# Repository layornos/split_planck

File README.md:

# Custom Keyboard - Split Ortholinear Keyboard (split planck)

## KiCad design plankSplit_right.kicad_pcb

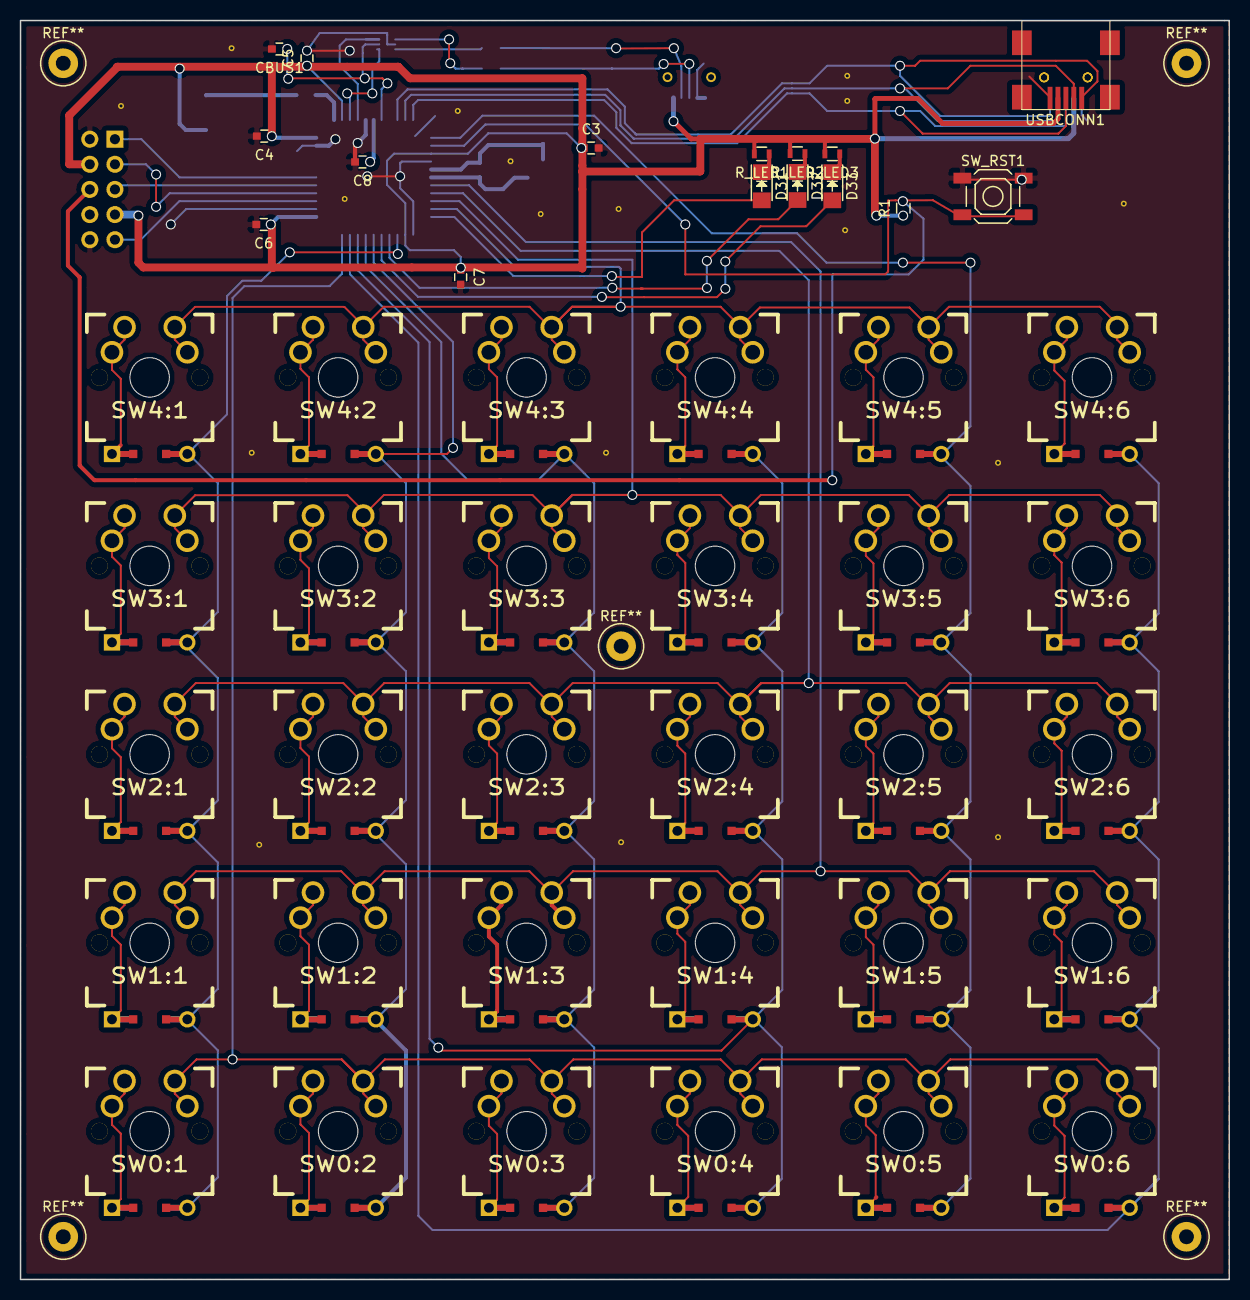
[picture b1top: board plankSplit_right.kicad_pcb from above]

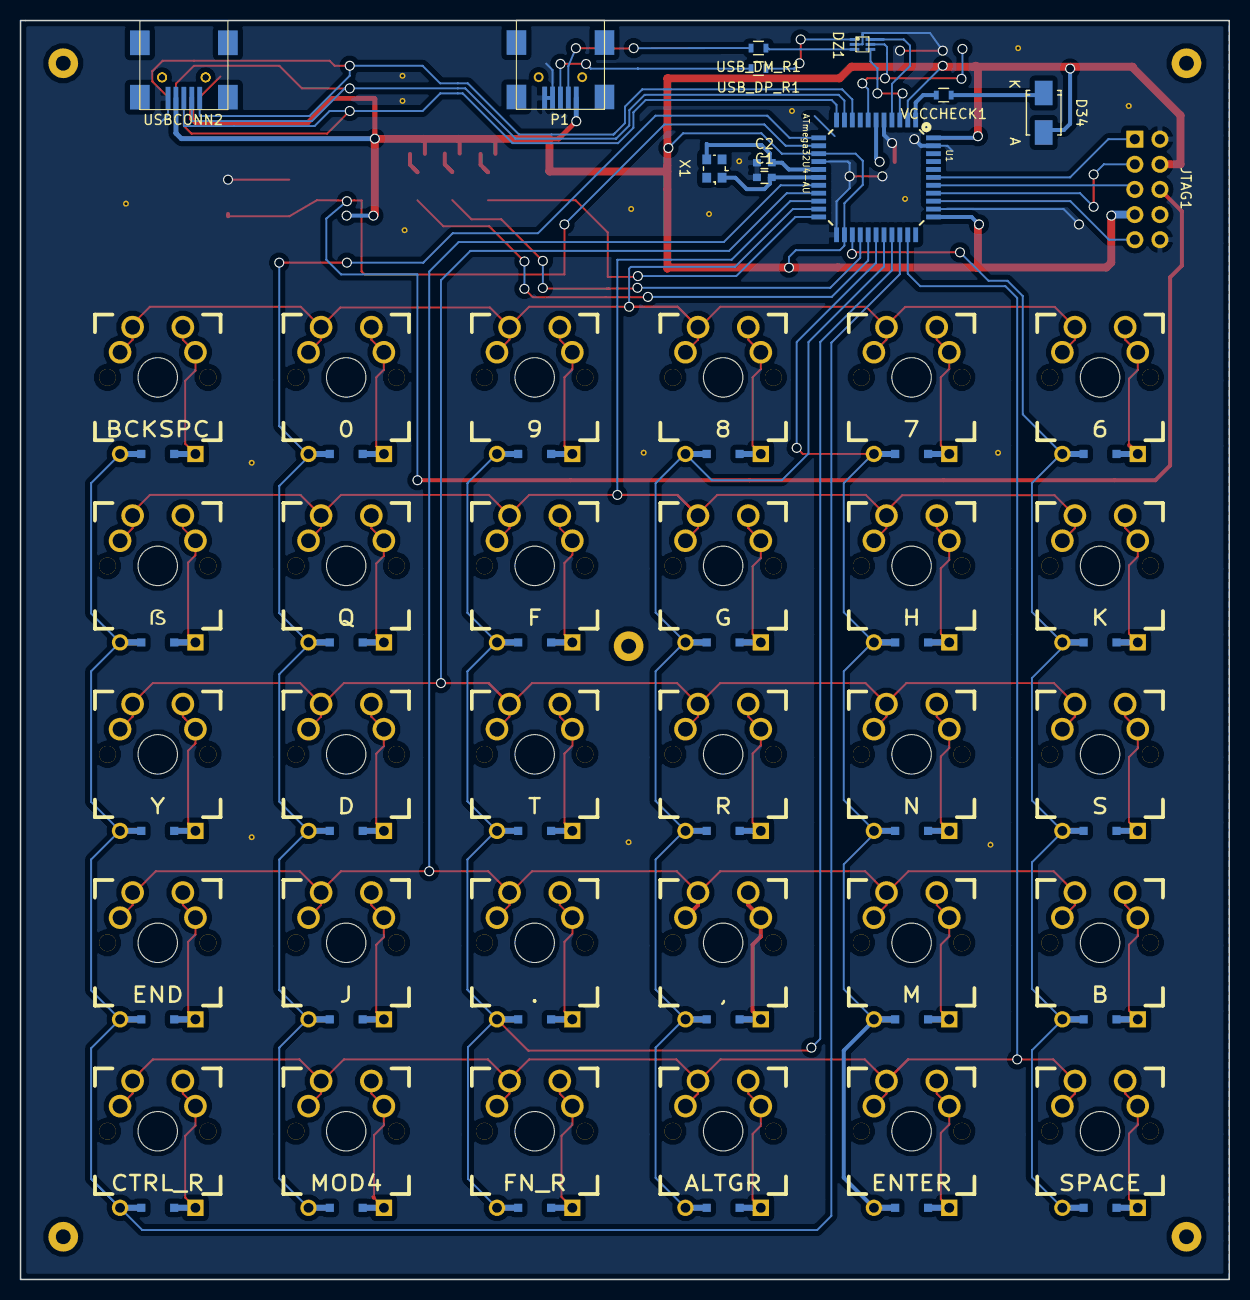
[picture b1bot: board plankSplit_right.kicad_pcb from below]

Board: 2 copper layers, 122.2 x 127.3 mm, 88 parts (12 on the bottom side), 69 nets.

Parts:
C1, C2: 22pF; C_0603
C3, C4, C5, C6, C7: 100nF; C_0603
C8: 1uF; C_0603
CBUS1: 100nF; C_0603
D1: D4:0; DIODE
D2: D3:0; DIODE
D3: D2:0; DIODE
D4: D1:0; DIODE
D5: D0:0; DIODE
D6: D4:1; DIODE
D7: D3:1; DIODE
D8: D2:1; DIODE
D9: D1:1; DIODE
D10: D0:1; DIODE
D11: D4:2; DIODE
D12: D3:2; DIODE
D13: D2:2; DIODE
D14: D1:2; DIODE
D15: D0:2; DIODE
D16: D4:3; DIODE
D17: D3:3; DIODE
D18: D2:3; DIODE
D19: D1:3; DIODE
D20: D0:3; DIODE
D21: D4:4; DIODE
D22: D3:4; DIODE
D23: D2:4; DIODE
D24: D1:4; DIODE
D25: D0:4; DIODE
D26: D4:5; DIODE
D27: D3:5; DIODE
D28: D2:5; DIODE
D29: D1:5; DIODE
D30: D0:5; DIODE
D31, D32, D33: LED; LED_1206
D34: D; SMA_Standard
DZ1: USBLC6-2P6; usblc6-2p6
JTAG1: JTAG; IDC_Header_Straight_10pins
P1: USB_A; usb-b-mini-female
R1: 10k; R_0603
R_LED1, R_LED2, R_LED3: R220; R_0603
SW0:1: SPACE; MX_FLIP_DIODE_New
SW0:2: ENTER; MX_FLIP_DIODE_New
SW0:3: ALTGR; MX_FLIP_DIODE_New
SW0:4: FN_R; MX_FLIP_DIODE_New
SW0:5: MOD4; MX_FLIP_DIODE_New
SW0:6: CTRL_R; MX_FLIP_DIODE_New
SW1:1: B; MX_FLIP_DIODE_New
SW1:2: M; MX_FLIP_DIODE_New
SW1:3: ,; MX_FLIP_DIODE_New
SW1:4: .; MX_FLIP_DIODE_New
SW1:5: J; MX_FLIP_DIODE_New
SW1:6: END; MX_FLIP_DIODE_New
SW2:1: S; MX_FLIP_DIODE_New
SW2:2: N; MX_FLIP_DIODE_New
SW2:3: R; MX_FLIP_DIODE_New
SW2:4: T; MX_FLIP_DIODE_New
SW2:5: D; MX_FLIP_DIODE_New
SW2:6: Y; MX_FLIP_DIODE_New
SW3:1: K; MX_FLIP_DIODE_New
SW3:2: H; MX_FLIP_DIODE_New
SW3:3: G; MX_FLIP_DIODE_New
SW3:4: F; MX_FLIP_DIODE_New
SW3:5: Q; MX_FLIP_DIODE_New
SW3:6: ẞ; MX_FLIP_DIODE_New
SW4:1: 6; MX_FLIP_DIODE_New
SW4:2: 7; MX_FLIP_DIODE_New
SW4:3: 8; MX_FLIP_DIODE_New
SW4:4: 9; MX_FLIP_DIODE_New
SW4:5: 0; MX_FLIP_DIODE_New
SW4:6: BCKSPC; MX_FLIP_DIODE_New
SW_RST1: SWRST; SW_SPST_SKQG
U1: ATmega32U4-AU; TQFP44
USBCONN1, USBCONN2: CONN_5; usb-b-mini-female
USB_DM_R1: R; R_0603
USB_DP_R1: R; R_0603
VCCCHECK1: R47k; R_0603
X1: CRYSTAL; Crystal_SMD_2520_4Pads

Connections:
/COL0: D1.1, D2.1, D3.1, D4.1, D5.1, U1.25
/COL1: D6.1, D7.1, D8.1, D9.1, D10.1, U1.28
/COL2: D11.1, D12.1, D13.1, D14.1, D15.1, U1.29
/COL3: D16.1, D17.1, D18.1, D19.1, D20.1, U1.30
/COL4: D21.1, D22.1, D23.1, D24.1, D25.1, U1.12
/COL5: D26.1, D27.1, D28.1, D29.1, D30.1, U1.31
/D+in: DZ1.6, U1.4
/D+out: DZ1.1, USB_DP_R1.1
/D-in: DZ1.4, U1.3
/D-out: DZ1.3, USB_DM_R1.1
/DATA1: U1.10, USBCONN1.2, USBCONN2.2
/DATA2: U1.11, USBCONN1.3, USBCONN2.3
/LED1: D31.2, U1.22
/LED2: D32.2, U1.26
/LED3: D33.2, U1.27
/P1: U1.1, VCCCHECK1.2
/P14_VCC: C3.1, C4.1, C5.1, C6.1, C7.1, D34.2, JTAG1.4, JTAG1.7, P1.1, R1.1, R_LED1.2, R_LED2.2, R_LED3.2, U1.2, U1.14, U1.24, U1.34, U1.44, USBCONN1.4, USBCONN2.4
/ROW0: SW0:1.1, SW0:2.1, SW0:3.1, SW0:4.1, SW0:5.1, SW0:6.1, U1.32
/ROW1: SW1:1.1, SW1:2.1, SW1:3.1, SW1:4.1, SW1:5.1, SW1:6.1, U1.18
/ROW2: SW2:1.1, SW2:2.1, SW2:3.1, SW2:4.1, SW2:5.1, SW2:6.1, U1.19
/ROW3: SW3:1.1, SW3:2.1, SW3:3.1, SW3:4.1, SW3:5.1, SW3:6.1, U1.20
/ROW4: SW4:1.1, SW4:2.1, SW4:3.1, SW4:4.1, SW4:5.1, SW4:6.1, U1.21
/RST: JTAG1.6, R1.2, SW_RST1.2, U1.13
/SCLK: U1.9, USBCONN1.1, USBCONN2.1
/TCK: JTAG1.1, U1.39
/TDI: JTAG1.9, U1.36
/TDO: JTAG1.3, U1.37
/TMS: JTAG1.5, U1.38
/UCAP: C8.1, U1.6
/UGND: C1.1, C2.1, C3.2, C4.2, C5.2, C6.2, C7.2, C8.2, CBUS1.2, DZ1.2, JTAG1.2, JTAG1.10, P1.4, P1.5, SW_RST1.1, U1.5, U1.15, U1.23, U1.35, U1.43, USBCONN1.5, USBCONN2.5
/VBus: CBUS1.1, DZ1.5, U1.7
/XTAL1: C1.2, U1.17, X1.1
/XTAL2: C2.2, U1.16, X1.2
unnamed: D1.2, SW4:1.2
unnamed: D2.2, SW3:1.2
unnamed: D3.2, SW2:1.2
unnamed: D4.2, SW1:1.2
unnamed: D5.2, SW0:1.2
unnamed: D6.2, SW4:2.2
unnamed: D7.2, SW3:2.2
unnamed: D8.2, SW2:2.2
unnamed: D9.2, SW1:2.2
unnamed: D10.2, SW0:2.2
unnamed: D11.2, SW4:3.2
unnamed: D12.2, SW3:3.2
unnamed: D13.2, SW2:3.2
unnamed: D14.2, SW1:3.2
unnamed: D15.2, SW0:3.2
unnamed: D16.2, SW4:4.2
unnamed: D17.2, SW3:4.2
unnamed: D18.2, SW2:4.2
unnamed: D19.2, SW1:4.2
unnamed: D20.2, SW0:4.2
unnamed: D21.2, SW4:5.2
unnamed: D22.2, SW3:5.2
unnamed: D23.2, SW2:5.2
unnamed: D24.2, SW1:5.2
unnamed: D25.2, SW0:5.2
unnamed: D26.2, SW4:6.2
unnamed: D27.2, SW3:6.2
unnamed: D28.2, SW2:6.2
unnamed: D29.2, SW1:6.2
unnamed: D30.2, SW0:6.2
unnamed: D31.1, R_LED1.1
unnamed: D32.1, R_LED2.1
unnamed: D33.1, R_LED3.1
unnamed: D34.1, VCCCHECK1.1
unnamed: P1.2, USB_DM_R1.2
unnamed: P1.3, USB_DP_R1.2

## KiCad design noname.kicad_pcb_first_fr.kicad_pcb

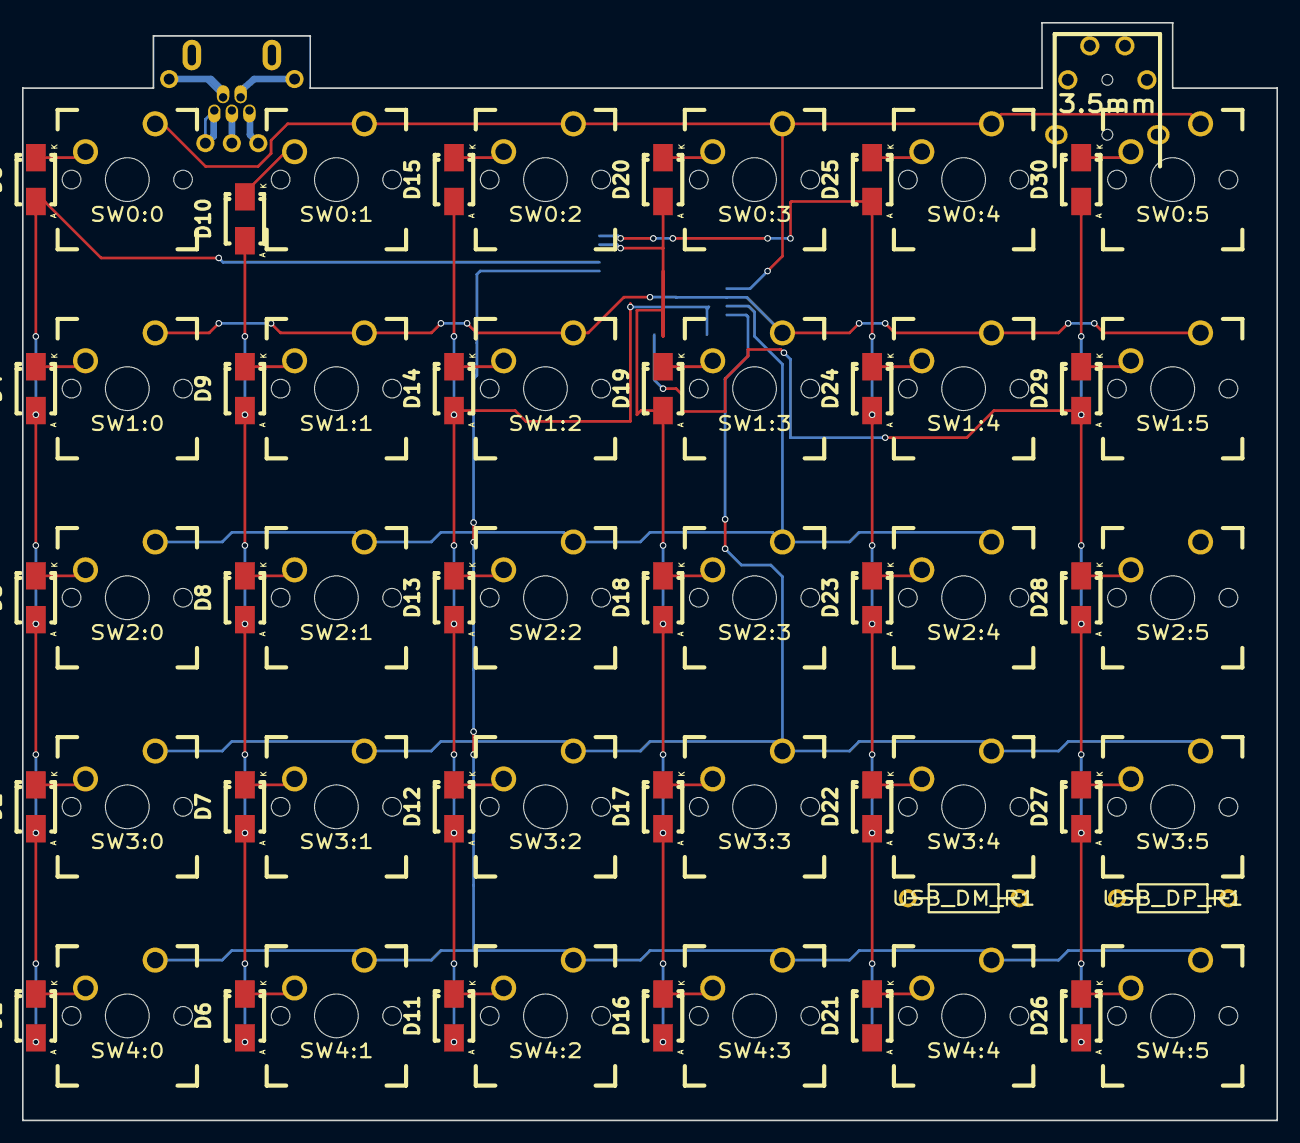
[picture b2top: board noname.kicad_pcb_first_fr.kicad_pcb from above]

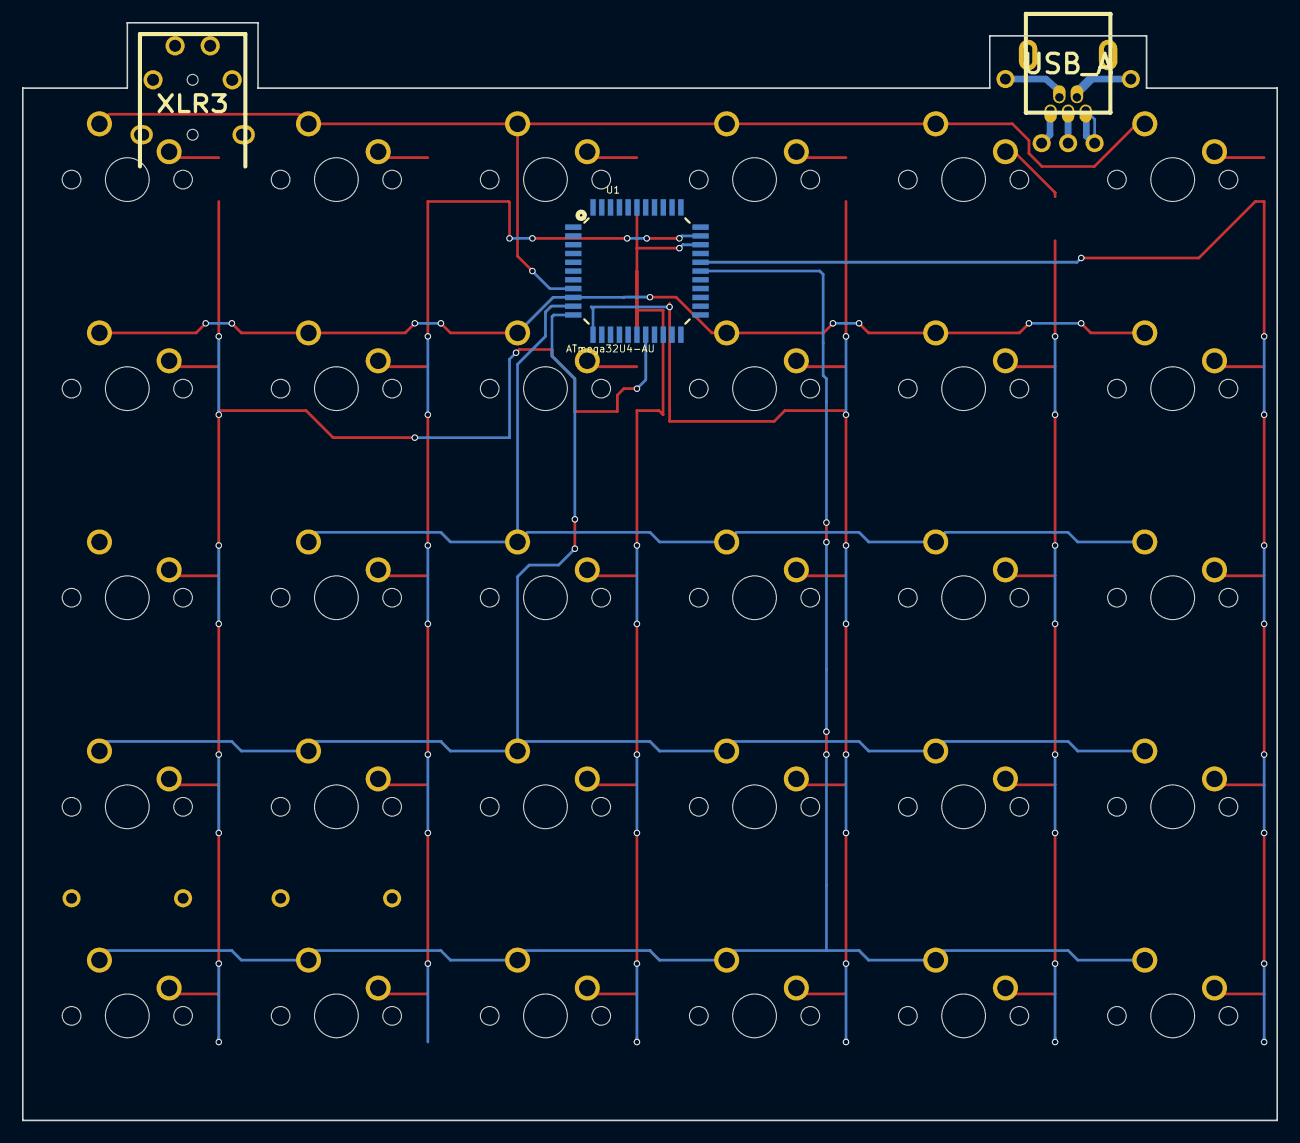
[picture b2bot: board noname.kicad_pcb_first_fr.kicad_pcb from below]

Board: 2 copper layers, 114.3 x 100.0 mm, 65 parts (3 on the bottom side), 46 nets.

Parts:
D1: D4:0; Diode-SMA_Standard_RevA_26July2010
D2: D3:0; Diode-SMA_Standard_RevA_26July2010
D3: D2:0; Diode-SMA_Standard_RevA_26July2010
D4: D1:0; Diode-SMA_Standard_RevA_26July2010
D5: D0:0; Diode-SMA_Standard_RevA_26July2010
D6: D4:1; Diode-SMA_Standard_RevA_26July2010
D7: D3:1; Diode-SMA_Standard_RevA_26July2010
D8: D2:1; Diode-SMA_Standard_RevA_26July2010
D9: D1:1; Diode-SMA_Standard_RevA_26July2010
D10: D0:1; Diode-SMA_Standard_RevA_26July2010
D11: D4:2; Diode-SMA_Standard_RevA_26July2010
D12: D3:2; Diode-SMA_Standard_RevA_26July2010
D13: D2:2; Diode-SMA_Standard_RevA_26July2010
D14: D1:2; Diode-SMA_Standard_RevA_26July2010
D15: D0:2; Diode-SMA_Standard_RevA_26July2010
D16: D4:3; Diode-SMA_Standard_RevA_26July2010
D17: D3:3; Diode-SMA_Standard_RevA_26July2010
D18: D2:3; Diode-SMA_Standard_RevA_26July2010
D19: D1:3; Diode-SMA_Standard_RevA_26July2010
D20: D0:3; Diode-SMA_Standard_RevA_26July2010
D21: D4:4; Diode-SMA_Standard_RevA_26July2010
D22: D3:4; Diode-SMA_Standard_RevA_26July2010
D23: D2:4; Diode-SMA_Standard_RevA_26July2010
D24: D1:4; Diode-SMA_Standard_RevA_26July2010
D25: D0:4; Diode-SMA_Standard_RevA_26July2010
D26: D4:5; Diode-SMA_Standard_RevA_26July2010
D27: D3:5; Diode-SMA_Standard_RevA_26July2010
D28: D2:5; Diode-SMA_Standard_RevA_26July2010
D29: D1:5; Diode-SMA_Standard_RevA_26July2010
D30: D0:5; Diode-SMA_Standard_RevA_26July2010
K1: XLR3; 4pin35mmAudio
P1: USB_A; USBMINImod
SW0:0: SPACE; CHERRY_PCB_100H
SW0:1: ENTER; CHERRY_PCB_100H
SW0:2: ALTGR; CHERRY_PCB_100H
SW0:3: FN_R; CHERRY_PCB_100H
SW0:4: MOD4; CHERRY_PCB_100H
SW0:5: CTRL_R; CHERRY_PCB_100H
SW1:0: B; CHERRY_PCB_100H
SW1:1: M; CHERRY_PCB_100H
SW1:2: ,; CHERRY_PCB_100H
SW1:3: .; CHERRY_PCB_100H
SW1:4: J; CHERRY_PCB_100H
SW1:5: END; CHERRY_PCB_100H
SW2:0: S; CHERRY_PCB_100H
SW2:1: N; CHERRY_PCB_100H
SW2:2: R; CHERRY_PCB_100H
SW2:3: T; CHERRY_PCB_100H
SW2:4: D; CHERRY_PCB_100H
SW2:5: Y; CHERRY_PCB_100H
SW3:0: K; CHERRY_PCB_100H
SW3:1: H; CHERRY_PCB_100H
SW3:2: G; CHERRY_PCB_100H
SW3:3: F; CHERRY_PCB_100H
SW3:4: Q; CHERRY_PCB_100H
SW3:5: ẞ; CHERRY_PCB_100H
SW4:0: 6; CHERRY_PCB_100H
SW4:1: 7; CHERRY_PCB_100H
SW4:2: 8; CHERRY_PCB_100H
SW4:3: 9; CHERRY_PCB_100H
SW4:4: 0; CHERRY_PCB_100H
SW4:5: BCKSPC; CHERRY_PCB_100H
U1: ATmega32U4-AU; TQFP44
USB_DM_R1: R; RESISTOR
USB_DP_R1: R; RESISTOR

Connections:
/COL0: D1.1, D2.1, D3.1, D4.1, D5.1, U1.29
/COL1: D6.1, D7.1, D8.1, D9.1, D10.1, U1.30
/COL2: D11.1, D12.1, D13.1, D14.1, D15.1, U1.12
/COL3: D16.1, D17.1, D18.1, D19.1, D20.1, U1.31
/COL4: D21.1, D22.1, D23.1, D24.1, D25.1, U1.32
/COL5: D26.1, D27.1, D28.1, D29.1, D30.1, U1.18
/DATA: K1.1, U1.19
/ROW0: SW0:0.1, SW0:1.1, SW0:2.1, SW0:3.1, SW0:4.1, SW0:5.1, U1.8
/ROW1: SW1:0.1, SW1:1.1, SW1:2.1, SW1:3.1, SW1:4.1, SW1:5.1, U1.9
/ROW2: SW2:0.1, SW2:1.1, SW2:2.1, SW2:3.1, SW2:4.1, SW2:5.1, U1.10
/ROW3: SW3:0.1, SW3:1.1, SW3:2.1, SW3:3.1, SW3:4.1, SW3:5.1, U1.11
/ROW4: SW4:0.1, SW4:1.1, SW4:2.1, SW4:3.1, SW4:4.1, SW4:5.1, U1.28
/USB_GND: P1.4, U1.5
/USB_VCC: P1.1, U1.2
GND: K1.3, U1.35
unnamed: D1.2, SW4:0.2
unnamed: D2.2, SW3:0.2
unnamed: D3.2, SW2:0.2
unnamed: D4.2, SW1:0.2
unnamed: D5.2, SW0:0.2
unnamed: D6.2, SW4:1.2
unnamed: D7.2, SW3:1.2
unnamed: D8.2, SW2:1.2
unnamed: D9.2, SW1:1.2
unnamed: D10.2, SW0:1.2
unnamed: D11.2, SW4:2.2
unnamed: D12.2, SW3:2.2
unnamed: D13.2, SW2:2.2
unnamed: D14.2, SW1:2.2
unnamed: D15.2, SW0:2.2
unnamed: D16.2, SW4:3.2
unnamed: D17.2, SW3:3.2
unnamed: D18.2, SW2:3.2
unnamed: D19.2, SW1:3.2
unnamed: D20.2, SW0:3.2
unnamed: D21.2, SW4:4.2
unnamed: D22.2, SW3:4.2
unnamed: D23.2, SW2:4.2
unnamed: D24.2, SW1:4.2
unnamed: D25.2, SW0:4.2
unnamed: D26.2, SW4:5.2
unnamed: D27.2, SW3:5.2
unnamed: D28.2, SW2:5.2
unnamed: D29.2, SW1:5.2
unnamed: D30.2, SW0:5.2
VCC: K1.2, U1.14

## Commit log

2016-08-06 init
2016-08-06 create rm
2016-08-06 added jtag and some capacitors
2016-08-06 margin updated
2016-08-07 Added more vias
2016-08-10 some footprints and track redraw
2016-09-07 Rev1.0
2016-10-15 change text
